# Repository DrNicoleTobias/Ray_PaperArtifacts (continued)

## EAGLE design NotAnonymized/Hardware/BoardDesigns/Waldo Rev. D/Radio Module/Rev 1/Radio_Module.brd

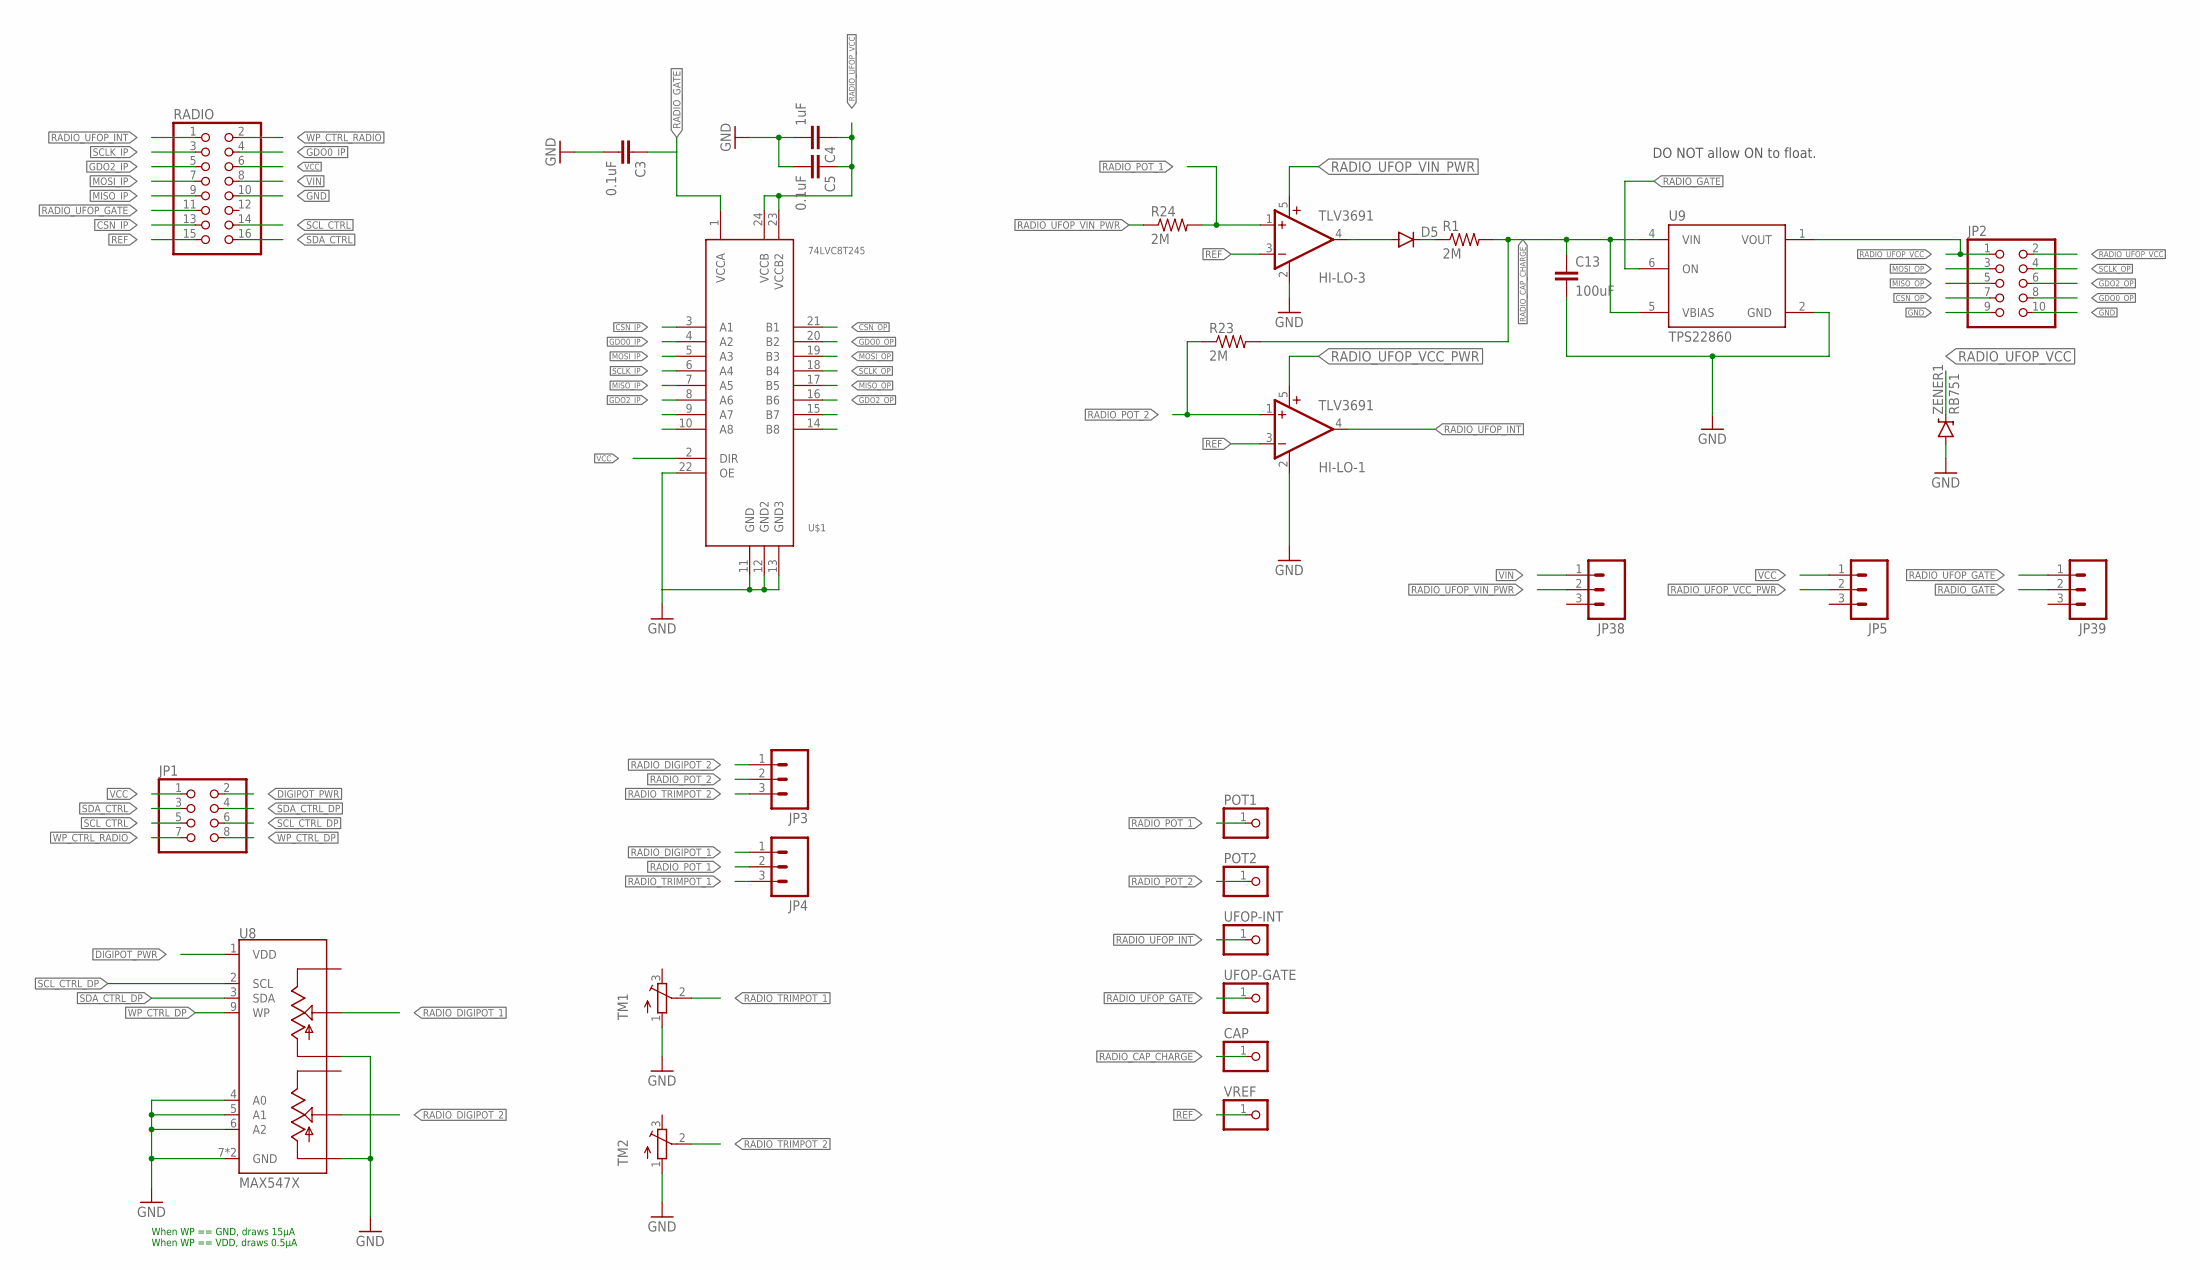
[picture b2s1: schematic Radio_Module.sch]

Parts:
C3, C5: 0.1uF; 0805
C4: 1uF; 0805
C13: 100uF; 0805; DIGIKEY 490-9969-1-ND
CAP: PINHD-1X1; 1X01
D5: DIODESOD523; SOD523
HI-LO-1, HI-LO-3: TLV3691; SC70-5
JP1: PINHD-2X4; 2X04
JP2: PINHD-2X5; 2X05
JP3, JP4, JP5, JP38, JP39: M03; 1X03-1.27MM
POT1, POT2: PINHD-1X1; 1X01
R1, R23: 2M; 0805; DIGIKEY 311-2.00MHRCT-ND
R24: 2M; 0805
RADIO: PINHD-2X8/90; 2X08/90
TM1, TM2: TRIMPOTTC33X; TC33X
U8: MAX547X; QFN16; DIGIKEY MAX5479ETE+-ND
U9: TPS22860; TSOT23-6
U$1: 74LVC8T245; TSSOP24
UFOP-GATE: PINHD-1X1; 1X01
UFOP-INT: PINHD-1X1; 1X01
VREF: PINHD-1X1; 1X01
ZENER1: RB751; SOD-523

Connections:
CSN_IP: RADIO.13, U$1.3 (A1)
CSN_OP: JP2.7, U$1.21 (B1)
DIGIPOT_PWR: JP1.2, U8.1 (VDD)
GDO0_IP: RADIO.4, U$1.4 (A2)
GDO0_OP: JP2.8, U$1.20 (B2)
GDO2_IP: RADIO.5, U$1.8 (A6)
GDO2_OP: JP2.6, U$1.16 (B6)
GND: C3.2, C4.2, C5.2, C13.2, HI-LO-1.2 (GND), HI-LO-3.2 (GND), JP2.9, JP2.10, RADIO.10, TM1.1 (A), TM2.1 (A), U8.4 (A0), U8.5 (A1), U8.6 (A2), U8.7 (GND), U8.10 (LB), U8.13 (LA), U8.TH (GND), U9.2 (GND), U$1.11 (GND), U$1.12 (GND2), U$1.13 (GND3), U$1.22 (OE), ZENER1.ANODE (A)
MISO_IP: RADIO.9, U$1.7 (A5)
MISO_OP: JP2.5, U$1.17 (B5)
MOSI_IP: RADIO.7, U$1.5 (A3)
MOSI_OP: JP2.3, U$1.19 (B3)
unnamed: D5.C, R1.1
unnamed: D5.A, HI-LO-3.4 (OUT)
RADIO_CAP_CHARGE: C13.1, CAP.1, R1.2, R23.2, U9.4 (VIN), U9.5 (VBIAS)
RADIO_DIGIPOT_1: JP4.1, U8.14 (WA)
RADIO_DIGIPOT_2: JP3.1, U8.11 (WB)
RADIO_GATE: C3.1, JP39.2, U9.6 (ON), U$1.1 (VCCA)
RADIO_POT_1: HI-LO-3.1 (+IN), JP4.2, POT1.1, R24.2
RADIO_POT_2: HI-LO-1.1 (+IN), JP3.2, POT2.1, R23.1
RADIO_TRIMPOT_1: JP4.3, TM1.2 (S)
RADIO_TRIMPOT_2: JP3.3, TM2.2 (S)
RADIO_UFOP_GATE: JP39.1, RADIO.11, UFOP-GATE.1
RADIO_UFOP_INT: HI-LO-1.4 (OUT), RADIO.1, UFOP-INT.1
RADIO_UFOP_VCC: C4.1, C5.1, JP2.1, JP2.2, U9.1 (VOUT), U$1.23 (VCCB2), U$1.24 (VCCB), ZENER1.CATHODE (C)
RADIO_UFOP_VCC_PWR: HI-LO-1.5 (V+), JP5.2
RADIO_UFOP_VIN_PWR: HI-LO-3.5 (V+), JP38.2, R24.1
REF: HI-LO-1.3 (-IN), HI-LO-3.3 (-IN), RADIO.15, VREF.1
SCLK_IP: RADIO.3, U$1.6 (A4)
SCLK_OP: JP2.4, U$1.18 (B4)
SCL_CTRL: JP1.5, RADIO.14
SCL_CTRL_DP: JP1.6, U8.2 (SCL)
SDA_CTRL: JP1.3, RADIO.16
SDA_CTRL_DP: JP1.4, U8.3 (SDA)
VCC: JP1.1, JP5.1, RADIO.6, U$1.2 (DIR)
VIN: JP38.1, RADIO.8
WP_CTRL_DP: JP1.8, U8.9 (WP)
WP_CTRL_RADIO: JP1.7, RADIO.2

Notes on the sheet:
DO NOT allow ON to float.
When WP == GND, draws 15µA When WP == VDD, draws 0.5µA

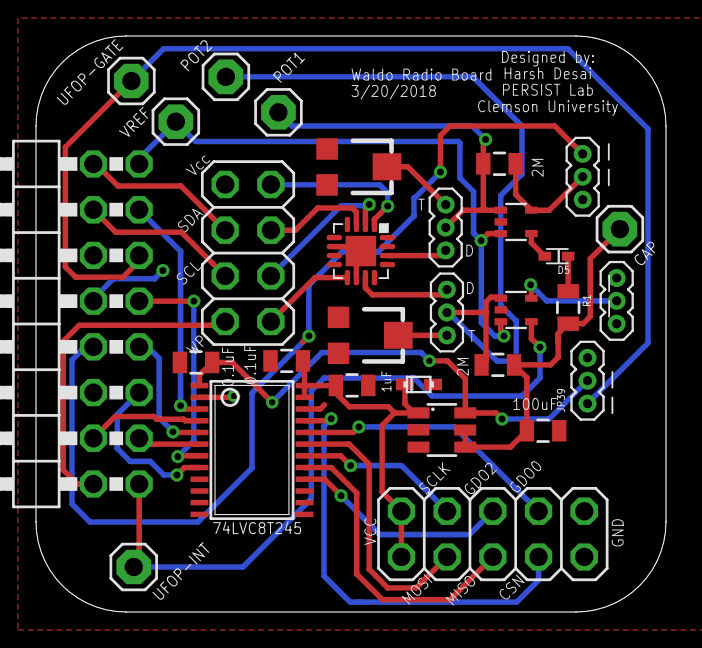
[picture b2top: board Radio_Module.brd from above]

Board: 2 copper layers, 35.0 x 32.0 mm, 30 parts (0 on the bottom side), 38 nets.

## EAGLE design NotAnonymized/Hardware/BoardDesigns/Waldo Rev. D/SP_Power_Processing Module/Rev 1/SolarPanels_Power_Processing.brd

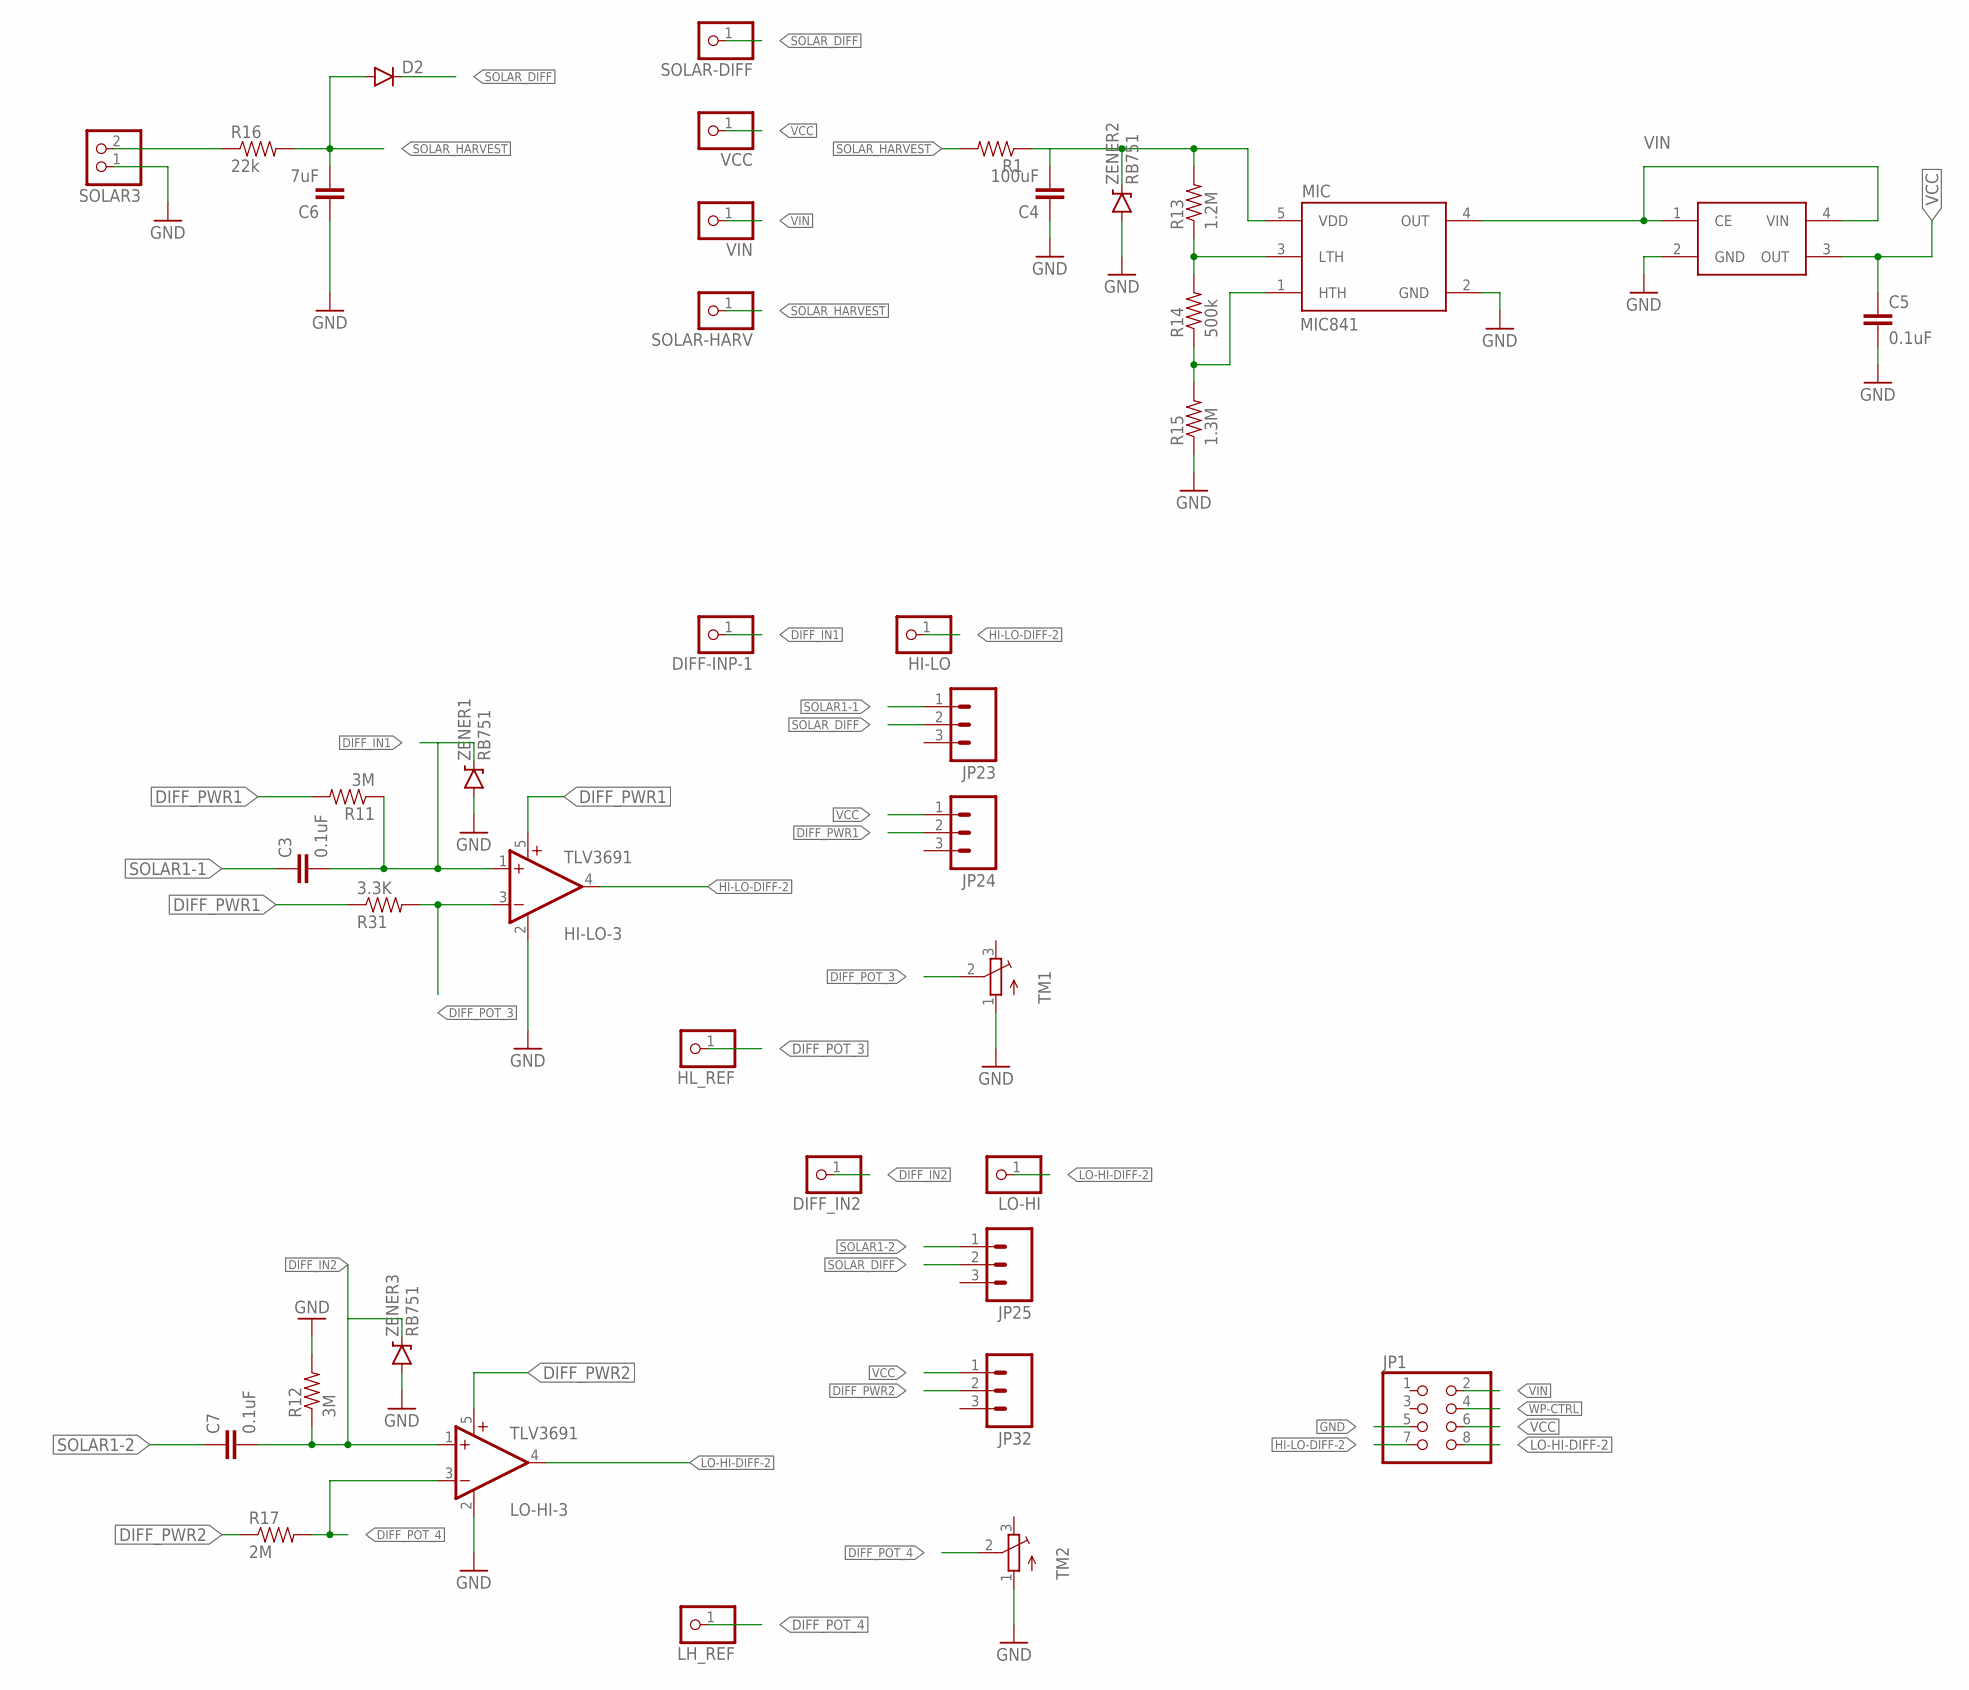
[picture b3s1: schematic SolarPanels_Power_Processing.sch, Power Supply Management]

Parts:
3.3K: R31; 0805
C3, C5, C7: 0.1uF; 0805
C4: 100uF; 0805
C6: 7uF; 0805
D2: DIODESOD523; SOD523
DIFF-INP-1: PINHD-1X1; 1X01
DIFF_IN2: PINHD-1X1; 1X01
HI-LO: PINHD-1X1; 1X01
HI-LO-3: TLV3691; SC70-5
HL_REF: PINHD-1X1; 1X01
JP1: PINHD-2X4/90; 2X04/90
JP23, JP24, JP25, JP32: M03; 1X03-1.27MM
LH_REF: PINHD-1X1; 1X01
LO-HI: PINHD-1X1; 1X01
LO-HI-3: TLV3691; SC70-5
MIC: MIC841; SC70-5
NCP: NCP583; SC82-AB_1PRIMARY
R1: RESISTOR0805-RES; 0805
R11, R12: 3M; 0805
R13: 1.2M; 0805
R14: 500k; 0805
R15: 1.3M; 0805
R16: 22k; 0805
R17: 2M; 0805
SOLAR3: PINHD-1X2; 1X02
SOLAR-DIFF: PINHD-1X1; 1X01
SOLAR-HARV: PINHD-1X1; 1X01
TM1, TM2: TRIMPOTTC33X; TC33X
VCC: PINHD-1X1; 1X01
VIN: PINHD-1X1; 1X01
ZENER1, ZENER2, ZENER3: RB751; SOD-523

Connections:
DIFF_IN1: C3.2, DIFF-INP-1.1, HI-LO-3.1 (+IN), R11.1, ZENER1.CATHODE (C)
DIFF_IN2: C7.2, DIFF_IN2.1, LO-HI-3.1 (+IN), R12.1, ZENER3.CATHODE (C)
DIFF_POT_3: 3.3K.2, HI-LO-3.3 (-IN), HL_REF.1, TM1.2 (S)
DIFF_POT_4: LH_REF.1, LO-HI-3.3 (-IN), R17.2, TM2.2 (S)
DIFF_PWR1: 3.3K.1, HI-LO-3.5 (V+), JP24.2, R11.2
DIFF_PWR2: JP32.2, LO-HI-3.5 (V+), R17.1
GND: C4.1, C5.2, C6.1, HI-LO-3.2 (GND), JP1.5, LO-HI-3.2 (GND), MIC.2 (GND), NCP.2 (GND), R12.2, R15.1, SOLAR3.1, TM1.1 (A), TM2.1 (A), ZENER1.ANODE (A), ZENER2.ANODE (A), ZENER3.ANODE (A)
HI-LO-DIFF-2: HI-LO.1, HI-LO-3.4 (OUT), JP1.7
LO-HI-DIFF-2: JP1.8, LO-HI.1, LO-HI-3.4 (OUT)
MIC_INPUT: C4.2, MIC.5 (VDD), R1.1, R13.2, ZENER2.CATHODE (C)
unnamed: MIC.3 (LTH), R13.1, R14.2
unnamed: MIC.1 (HTH), R14.1, R15.2
SOLAR1: R16.1, SOLAR3.2
SOLAR1-1: C3.1, JP23.1
SOLAR1-2: C7.1, JP25.1
SOLAR_DIFF: D2.C, JP23.2, JP25.2, SOLAR-DIFF.1
SOLAR_HARVEST: C6.2, D2.A, R1.2, R16.2, SOLAR-HARV.1
VCC: C5.1, JP1.6, JP24.1, JP32.1, NCP.3 (OUT), VCC.1
VIN: JP1.2, MIC.4 (OUT), NCP.1 (CE), NCP.4 (VIN), VIN.1
WP-CTRL: JP1.4

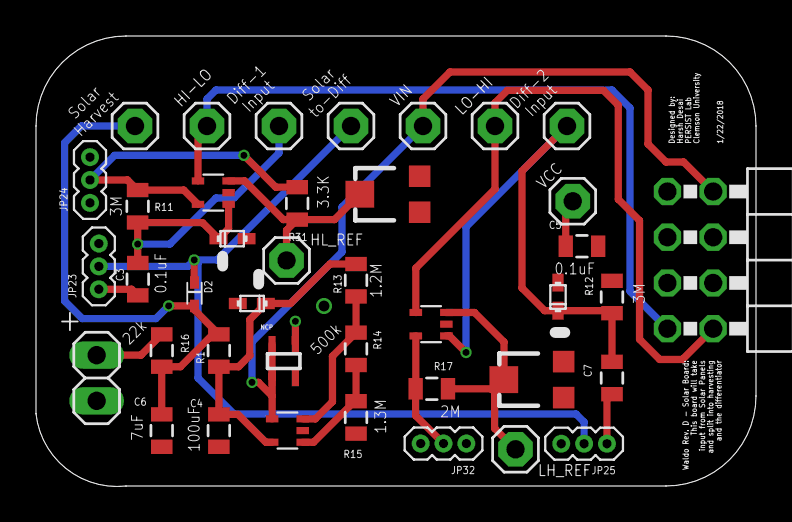
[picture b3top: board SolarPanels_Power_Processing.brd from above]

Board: 2 copper layers, 40.0 x 25.0 mm, 40 parts (0 on the bottom side), 19 nets.

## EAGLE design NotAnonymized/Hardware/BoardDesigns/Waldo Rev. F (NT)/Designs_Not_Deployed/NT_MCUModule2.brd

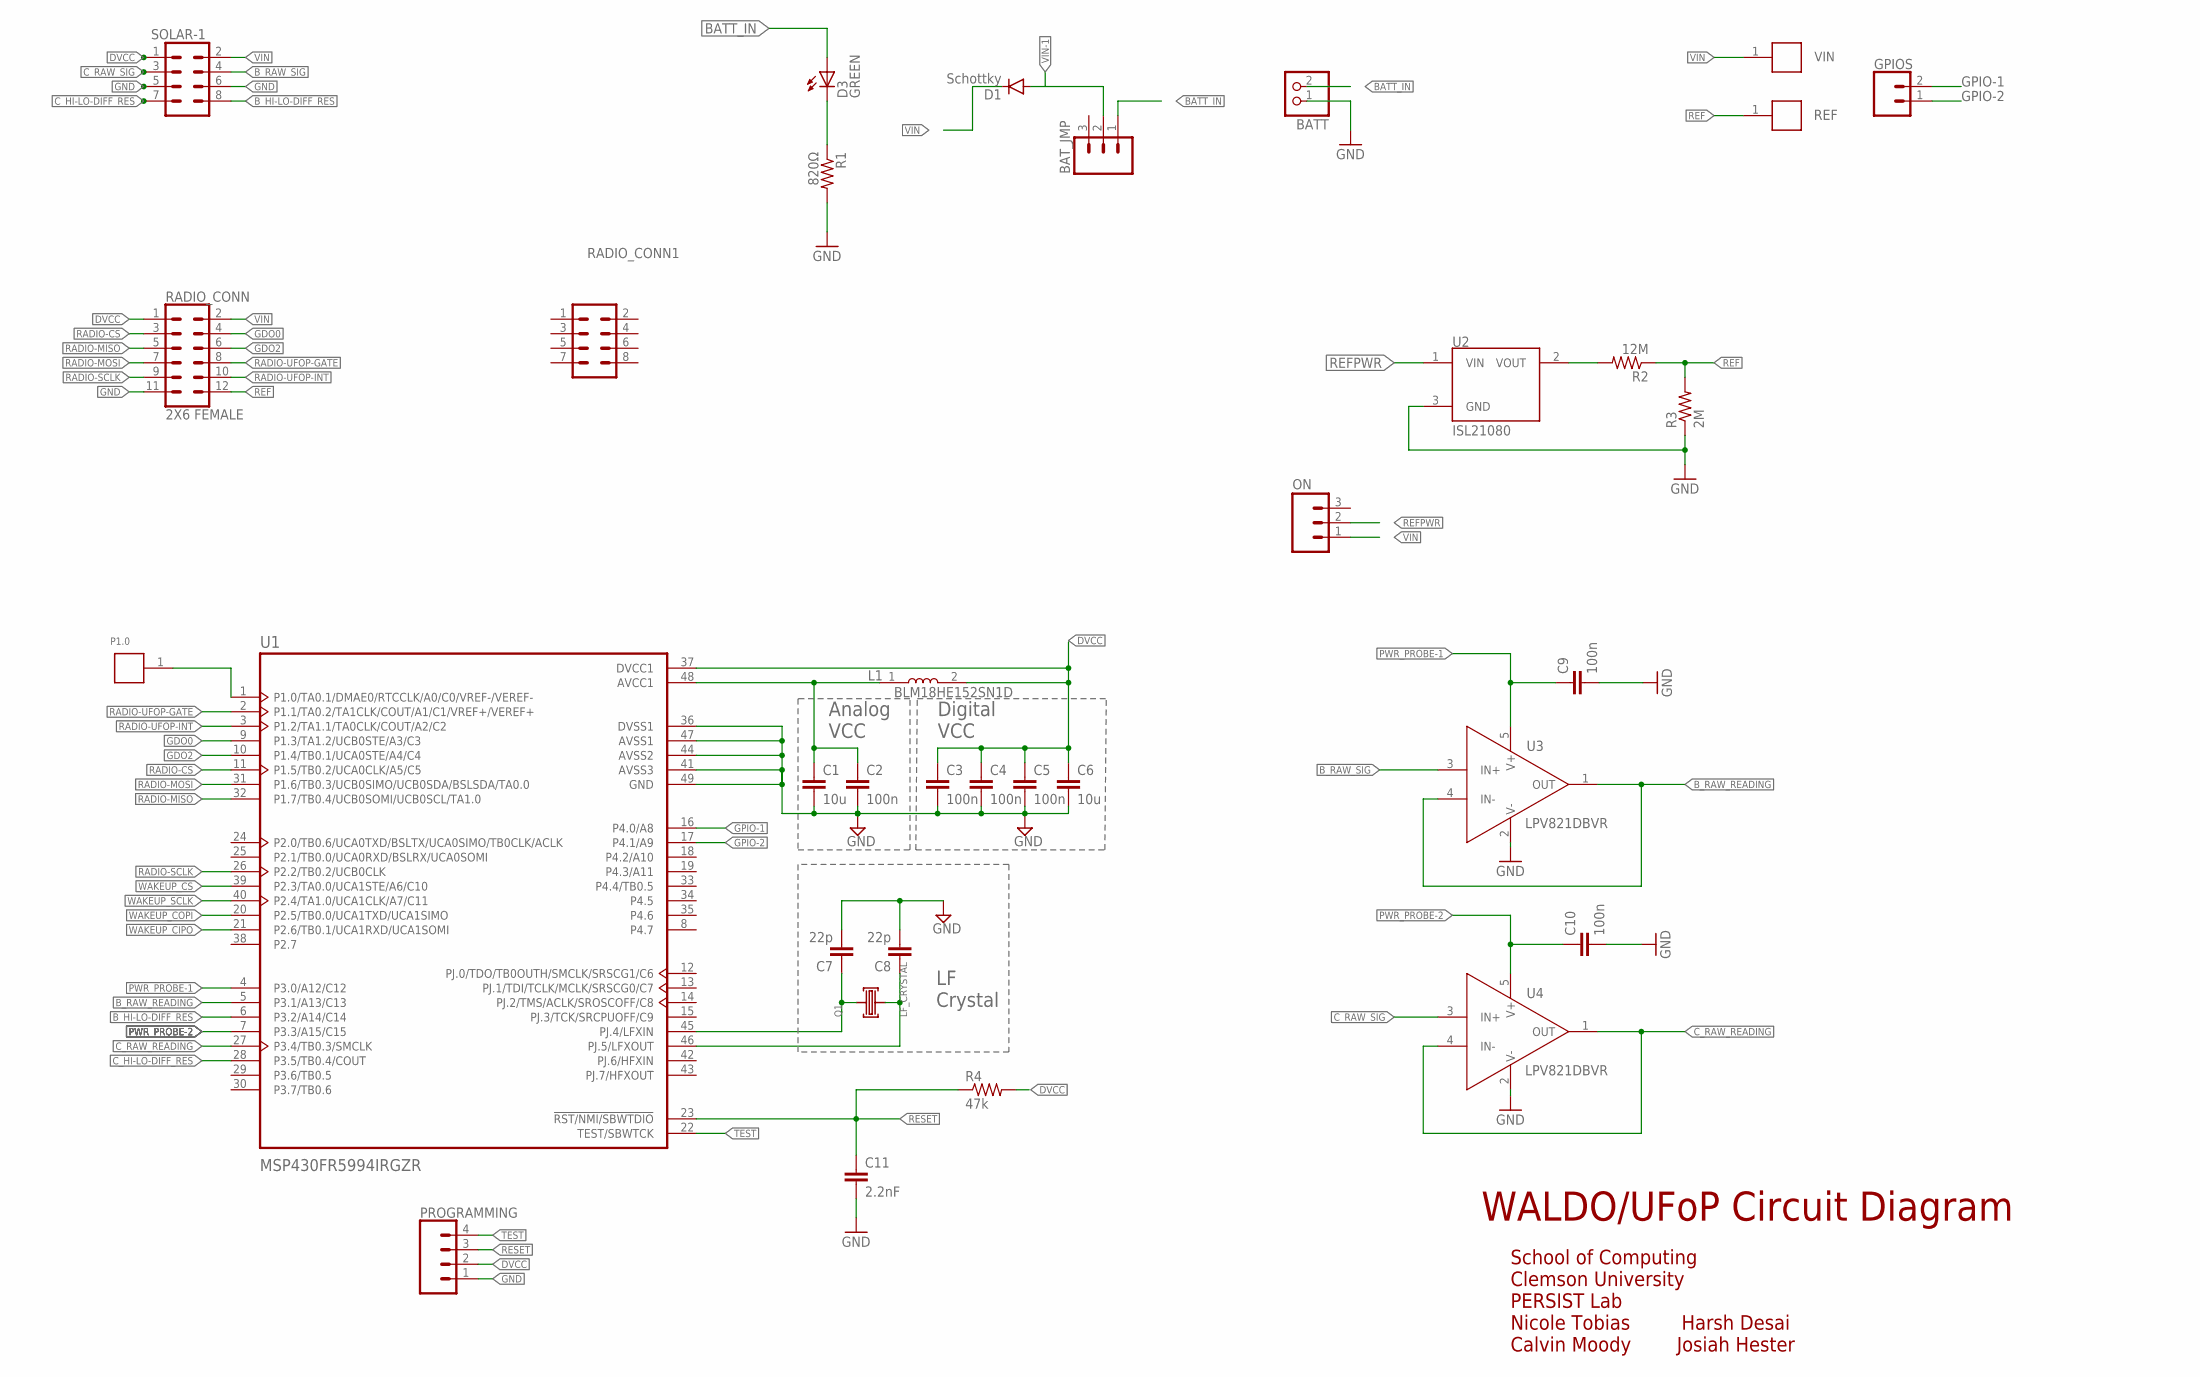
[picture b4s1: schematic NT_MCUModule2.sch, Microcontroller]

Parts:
BATT: PINHD-1X2; 1X02
BAT_JMP: M03; 1X03-1.27MM
C1, C6: 10u; C0603
C2, C3, C4, C5, C9, C10: 100n; C0603
C7, C8: 22p; C0603
C11: 2.2nF; C0603
D1: Schottky; SOD523
D3: GREEN; CHIP-LED0805
GPIOS: CONN_02; 1X02
L1: BLM18HE152SN1D; INDC1608X95
ON: M03; 1X03-1.27MM
P1.0: RCU-0C; TE_RCU-0C
PROGRAMMING: CONN_04; 1X04
Q1: LF_CRYSTAL
R1: 820Ω; 0603-RES
R2: 12M; 0603-RES; DIGIKEY 541-6.20MHCT-ND
R3: 2M; 0603-RES; DIGIKEY 311-1.00MHRCT-ND
R4: 47k; 0603-RES; DIGIKEY 311-1.00MHRCT-ND
RADIO_CONN: 2X6 FEMALE; 2X6
RADIO_CONN1: 2X6 FEMALE; 2X4
REF: RCU-0C; TE_RCU-0C
SOLAR-1: CONN_04X2; 2X4
U1: MSP430FR5994IRGZR; QFN50P700X700X100-49N
U2: ISL21080; SOT-23; DIGIKEY ISL21080DIH309Z-TKCT-ND
U3, U4: LPV821DBVR; SOT95P280X145-5N
VIN: RCU-0C; TE_RCU-0C

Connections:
AVCC: C1.1, C2.1, L1.1, U1.48 (AVCC1)
BATT_IN: BATT.2, BAT_JMP.1, D3.A
B_HI-LO-DIFF_RES: SOLAR-1.8, U1.6 (P3.2/A14/C14)
B_RAW_READING: U1.5 (P3.1/A13/C13), U3.1 (OUT), U3.4 (IN-)
B_RAW_SIG: SOLAR-1.4, U3.3 (IN+)
C_HI-LO-DIFF_RES: SOLAR-1.7, U1.28 (P3.5/TB0.4/COUT)
C_RAW_READING: U1.27 (P3.4/TB0.3/SMCLK), U4.1 (OUT), U4.4 (IN-)
C_RAW_SIG: SOLAR-1.3, U4.3 (IN+)
DVCC: C3.1, C4.1, C5.1, C6.1, L1.2, PROGRAMMING.2, R4.2, RADIO_CONN.1, SOLAR-1.1, U1.37 (DVCC1)
GDO0: RADIO_CONN.4, U1.9 (P1.3/TA1.2/UCB0STE/A3/C3)
GDO2: RADIO_CONN.6, U1.10 (P1.4/TB0.1/UCA0STE/A4/C4)
GND: BATT.1, C1.2, C2.2, C3.2, C4.2, C5.2, C6.2, C7.2, C8.2, C9.2, C10.2, C11.2, PROGRAMMING.1, R1.2, R3.1, RADIO_CONN.11, SOLAR-1.5, SOLAR-1.6, U1.36 (DVSS1), U1.41 (AVSS3), U1.44 (AVSS2), U1.47 (AVSS1), U1.49 (GND), U2.3 (GND), U3.2 (V-), U4.2 (V-)
GPIO-1: GPIOS.2, U1.16 (P4.0/A8)
GPIO-2: GPIOS.1, U1.17 (P4.1/A9)
unnamed: P1.0.1, U1.1 (P1.0/TA0.1/DMAE0/RTCCLK/A0/C0/VREF-/VER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)
unnamed: D3.C, R1.1
unnamed: R2.2, U2.2 (VOUT)
unnamed: C8.1, Q1.2, U1.46 (PJ.5/LFXOUT)
unnamed: C7.1, Q1.1, U1.45 (PJ.4/LFXIN)
PWR_PROBE-1: C9.1, U1.4 (P3.0/A12/C12), U3.5 (V+)
PWR_PROBE-2: C10.1, U1.7 (P3.3/A15/C15), U4.5 (V+)
RADIO-CS: RADIO_CONN.3, U1.11 (P1.5/TB0.2/UCA0CLK/A5/C5)
RADIO-MISO: RADIO_CONN.5, U1.32 (P1.7/TB0.4/UCB0SOMI/UCB0SCL/TA1.0)
RADIO-MOSI: RADIO_CONN.7, U1.31 (P1.6/TB0.3/UCB0SIMO/UCB0SDA/BSLSDA/TA0.0)
RADIO-SCLK: RADIO_CONN.9, U1.26 (P2.2/TB0.2/UCB0CLK)
RADIO-UFOP-GATE: RADIO_CONN.8, U1.2 (P1.1/TA0.2/TA1CLK/COUT/A1/C1/VREF+/VERE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)
RADIO-UFOP-INT: RADIO_CONN.10, U1.3 (P1.2/TA1.1/TA0CLK/COUT/A2/C2)
REF: R2.1, R3.2, RADIO_CONN.12, REF.1
REFPWR: ON.2, U2.1 (VIN)
RESET: C11.1, PROGRAMMING.3, R4.1, U1.23 (!RST/NMI/SBWTDIO)
TEST: PROGRAMMING.4, U1.22 (TEST/SBWTCK)
VIN: D1.C, ON.1, RADIO_CONN.2, SOLAR-1.2, VIN.1
VIN-1: BAT_JMP.2, D1.A
WAKEUP_CIPO: U1.21 (P2.6/TB0.1/UCA1RXD/UCA1SOMI)
WAKEUP_COPI: U1.20 (P2.5/TB0.0/UCA1TXD/UCA1SIMO)
WAKEUP_CS: U1.39 (P2.3/TA0.0/UCA1STE/A6/C10)
WAKEUP_SCLK: U1.40 (P2.4/TA1.0/UCA1CLK/A7/C11)

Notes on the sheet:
WALDO/UFoP Circuit Diagram
School of Computing Clemson University PERSIST Lab Nicole Tobias Harsh Desai Calvin Moody Josiah Hester
Analog
VCC
Digital
Crystal

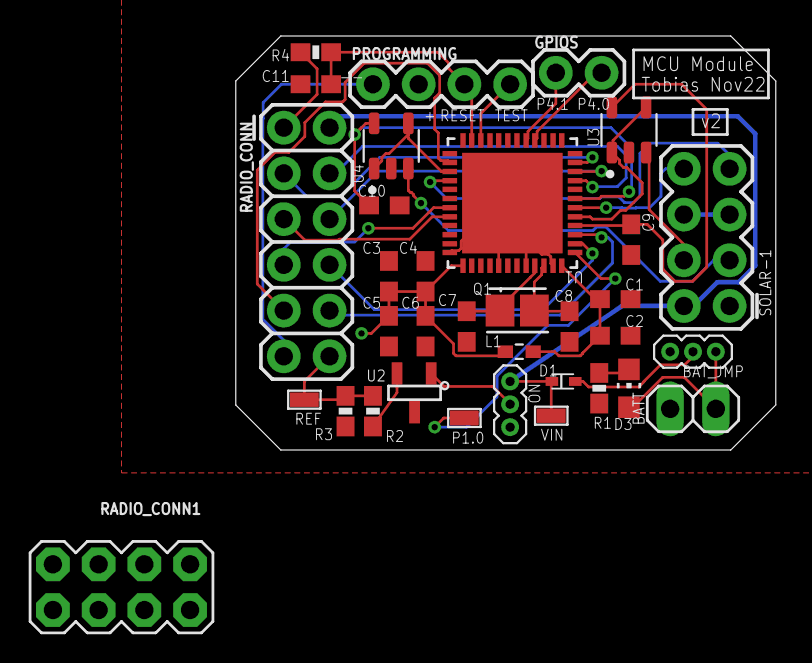
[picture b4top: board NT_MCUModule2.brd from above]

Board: 2 copper layers, 30.0 x 23.0 mm, 34 parts (0 on the bottom side), 33 nets.

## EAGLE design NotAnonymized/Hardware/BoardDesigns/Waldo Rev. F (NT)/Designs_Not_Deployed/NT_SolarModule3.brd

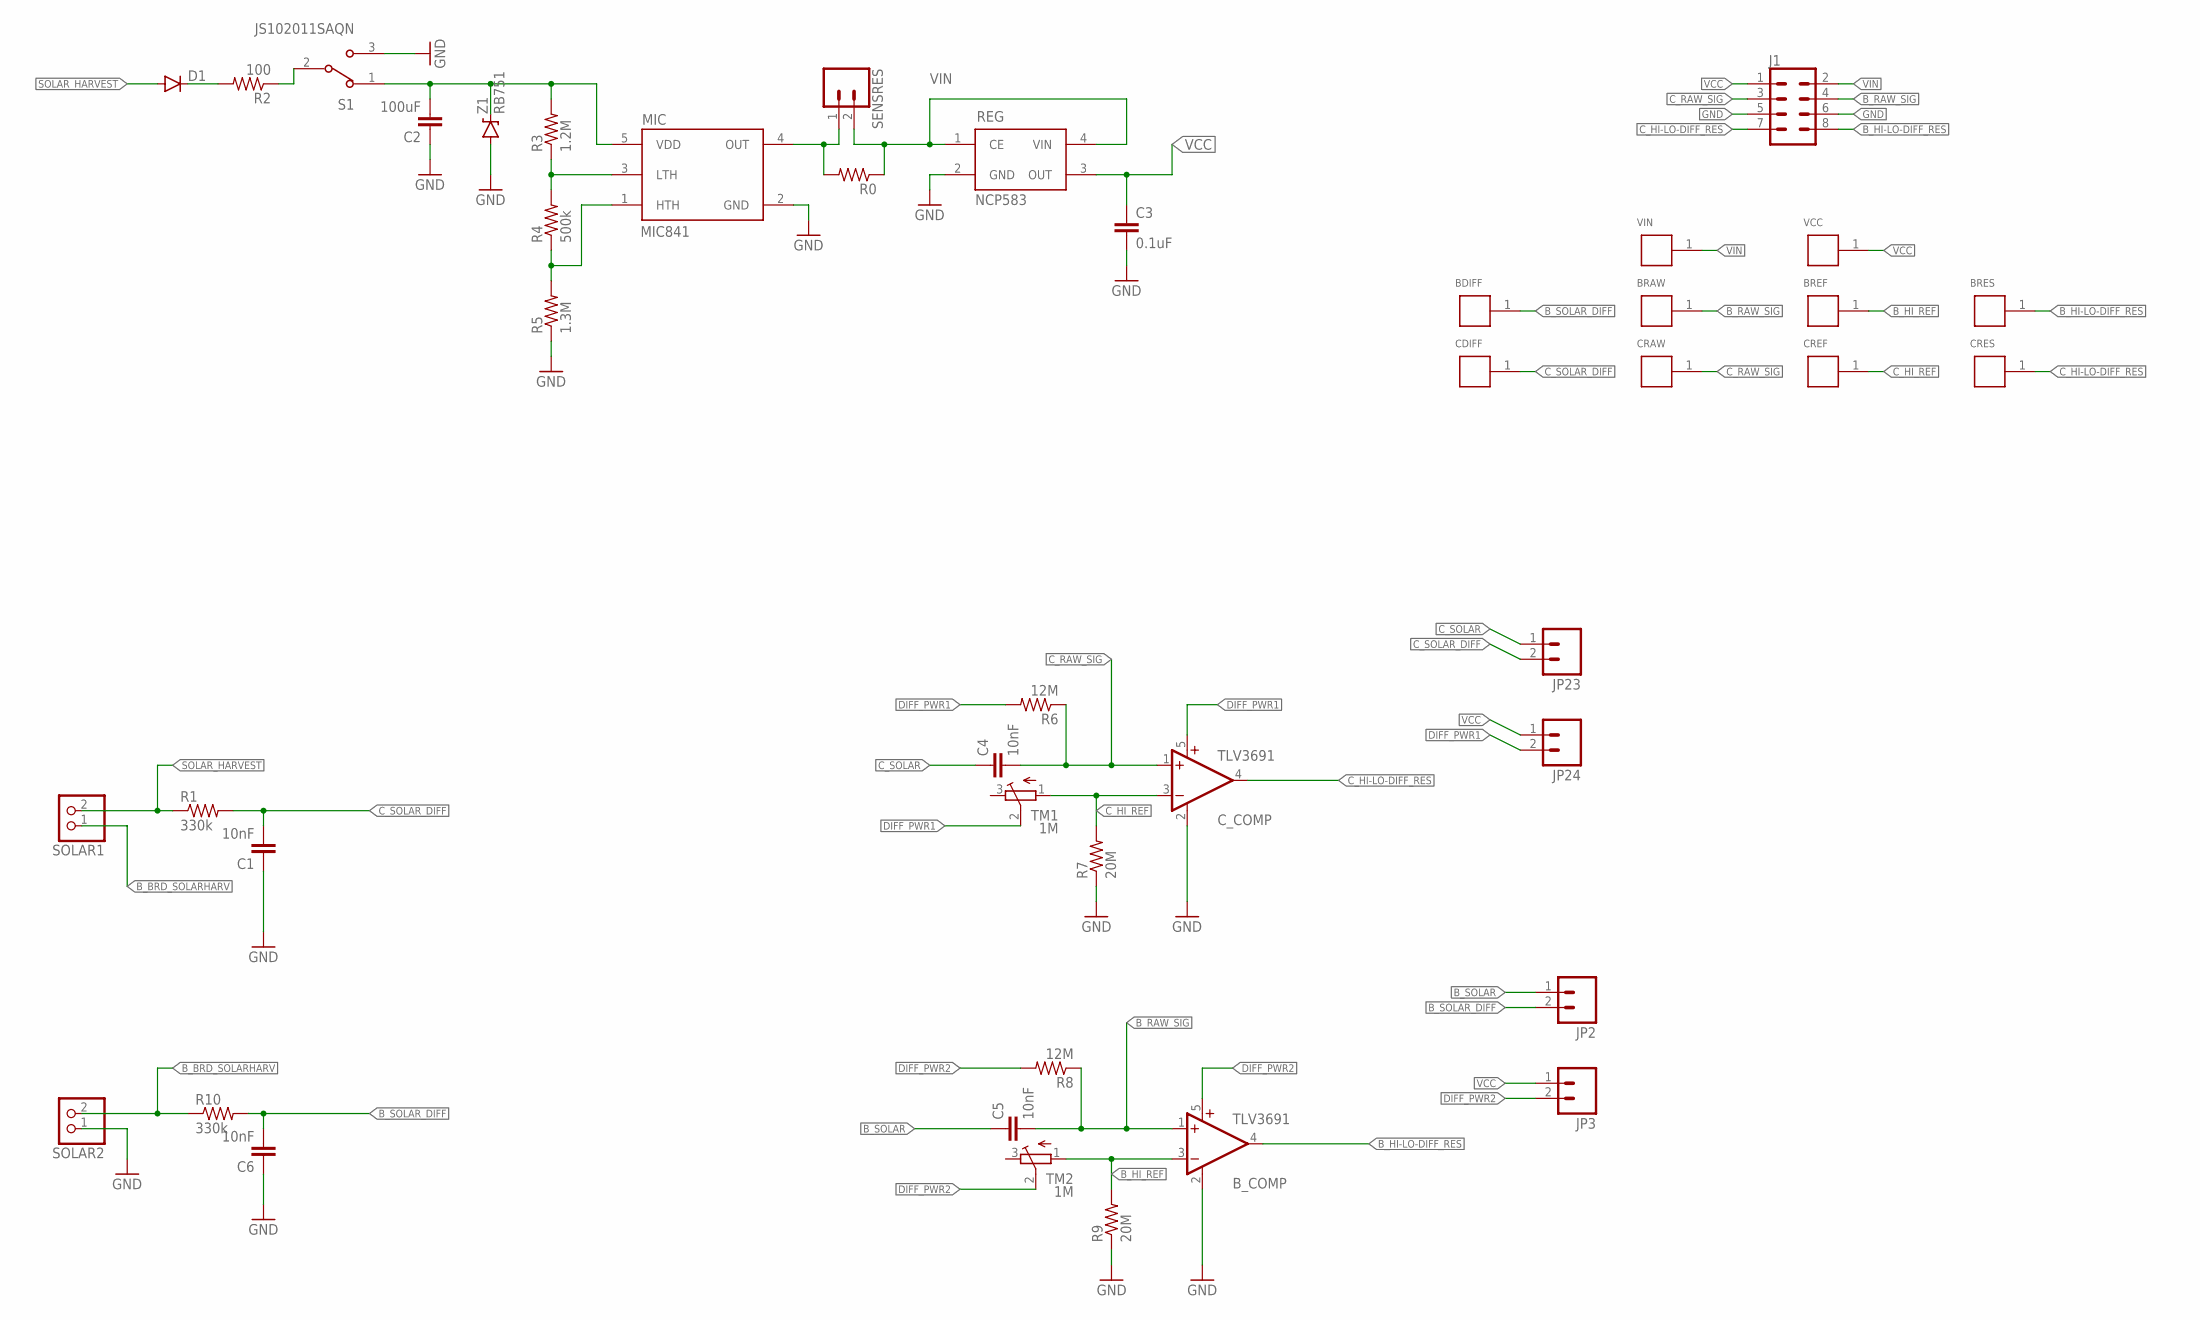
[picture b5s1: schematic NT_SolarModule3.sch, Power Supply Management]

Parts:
BDIFF: RCU-0C; TE_RCU-0C
BRAW: RCU-0C; TE_RCU-0C
BREF: RCU-0C; TE_RCU-0C
BRES: RCU-0C; TE_RCU-0C
B_COMP: TLV3691; SC70-5
C1, C4, C5, C6: 10nF; 0603-CAP
C2: 100uF; 0603-CAP
C3: 0.1uF; 0603-CAP
CDIFF: RCU-0C; TE_RCU-0C
CRAW: RCU-0C; TE_RCU-0C
CREF: RCU-0C; TE_RCU-0C
CRES: RCU-0C; TE_RCU-0C
C_COMP: TLV3691; SC70-5
D1: DIODESOD523; SOD523
J1: CONN_04X2; 2X4
JP2, JP3, JP23, JP24: M02; 1X02-1.27MM
MIC: MIC841; SC70-5
R0: RESISTOR0603; 0603-RES
R1, R10: 330k; 0603-RES
R2: 100; 0603-RES
R3: 1.2M; 0603-RES
R4: 500k; 0603-RES
R5: 1.3M; 0603-RES
R6, R8: 12M; 0603-RES
R7, R9: 20M; 0603-RES
REG: NCP583; SC82-AB_1PRIMARY
S1: JS102011SAQN; SW_JS102011SAQN
SENSRES: CONN_02; 1X02
SOLAR1, SOLAR2: PINHD-1X2; 1X02
TM1, TM2: 1M; TC33X
VCC: RCU-0C; TE_RCU-0C
VIN: RCU-0C; TE_RCU-0C
Z1: RB751; SOD-523

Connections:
B_BRD_SOLARHARV: R10.1, SOLAR1.1, SOLAR2.2
B_HI-LO-DIFF_RES: BRES.1, B_COMP.4 (OUT), J1.8
B_HI_REF: BREF.1, B_COMP.3 (-IN), R9.2, TM2.1 (A)
B_RAW_SIG: BRAW.1, B_COMP.1 (+IN), C5.2, J1.4, R8.1
B_SOLAR: C5.1, JP2.1
B_SOLAR_DIFF: BDIFF.1, C6.2, JP2.2, R10.2
C_HI-LO-DIFF_RES: CRES.1, C_COMP.4 (OUT), J1.7
C_HI_REF: CREF.1, C_COMP.3 (-IN), R7.2, TM1.1 (A)
C_RAW_SIG: C4.2, CRAW.1, C_COMP.1 (+IN), J1.3, R6.1
C_SOLAR: C4.1, JP23.1
C_SOLAR_DIFF: C1.2, CDIFF.1, JP23.2, R1.2
DIFF_PWR1: C_COMP.5 (V+), JP24.2, R6.2, TM1.2 (S)
DIFF_PWR2: B_COMP.5 (V+), JP3.2, R8.2, TM2.2 (S)
GND: B_COMP.2 (GND), C1.1, C2.1, C3.2, C6.1, C_COMP.2 (GND), J1.5, J1.6, MIC.2 (GND), R5.1, R7.1, R9.1, REG.2 (GND), S1.3, SOLAR2.1, Z1.ANODE (A)
MIC_INPUT: C2.2, MIC.5 (VDD), R3.2, S1.1, Z1.CATHODE (C)
unnamed: D1.C, R2.2
unnamed: MIC.4 (OUT), R0.2, SENSRES.1
unnamed: R2.1, S1.2
unnamed: MIC.3 (LTH), R3.1, R4.2
unnamed: MIC.1 (HTH), R4.1, R5.2
SOLAR_HARVEST: D1.A, R1.1, SOLAR1.2
VCC: C3.1, J1.1, JP3.1, JP24.1, REG.3 (OUT), VCC.1
VIN: J1.2, R0.1, REG.1 (CE), REG.4 (VIN), SENSRES.2, VIN.1

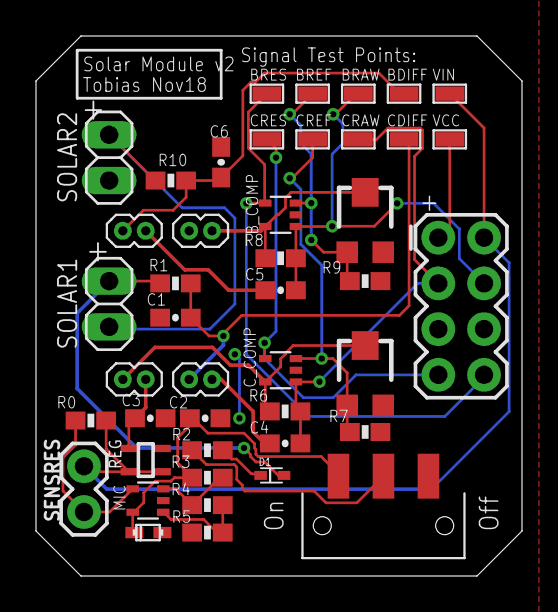
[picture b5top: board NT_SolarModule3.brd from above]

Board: 2 copper layers, 27.0 x 30.0 mm, 44 parts (0 on the bottom side), 23 nets.
